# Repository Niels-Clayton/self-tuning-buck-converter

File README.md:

# [Self Tuning Buck Converter](https://niels-clayton.github.io/self-tuning-buck-converter/)

### Documents

Documentation and project planing

### Literature

Latex bibliography `.bib` file, organised using [JabRef](http://www.jabref.org), with copies of all cited documents.

### Reports

Latex projects for all written reports.

- Project Proposal
- Preliminary Report
- Final Project Report

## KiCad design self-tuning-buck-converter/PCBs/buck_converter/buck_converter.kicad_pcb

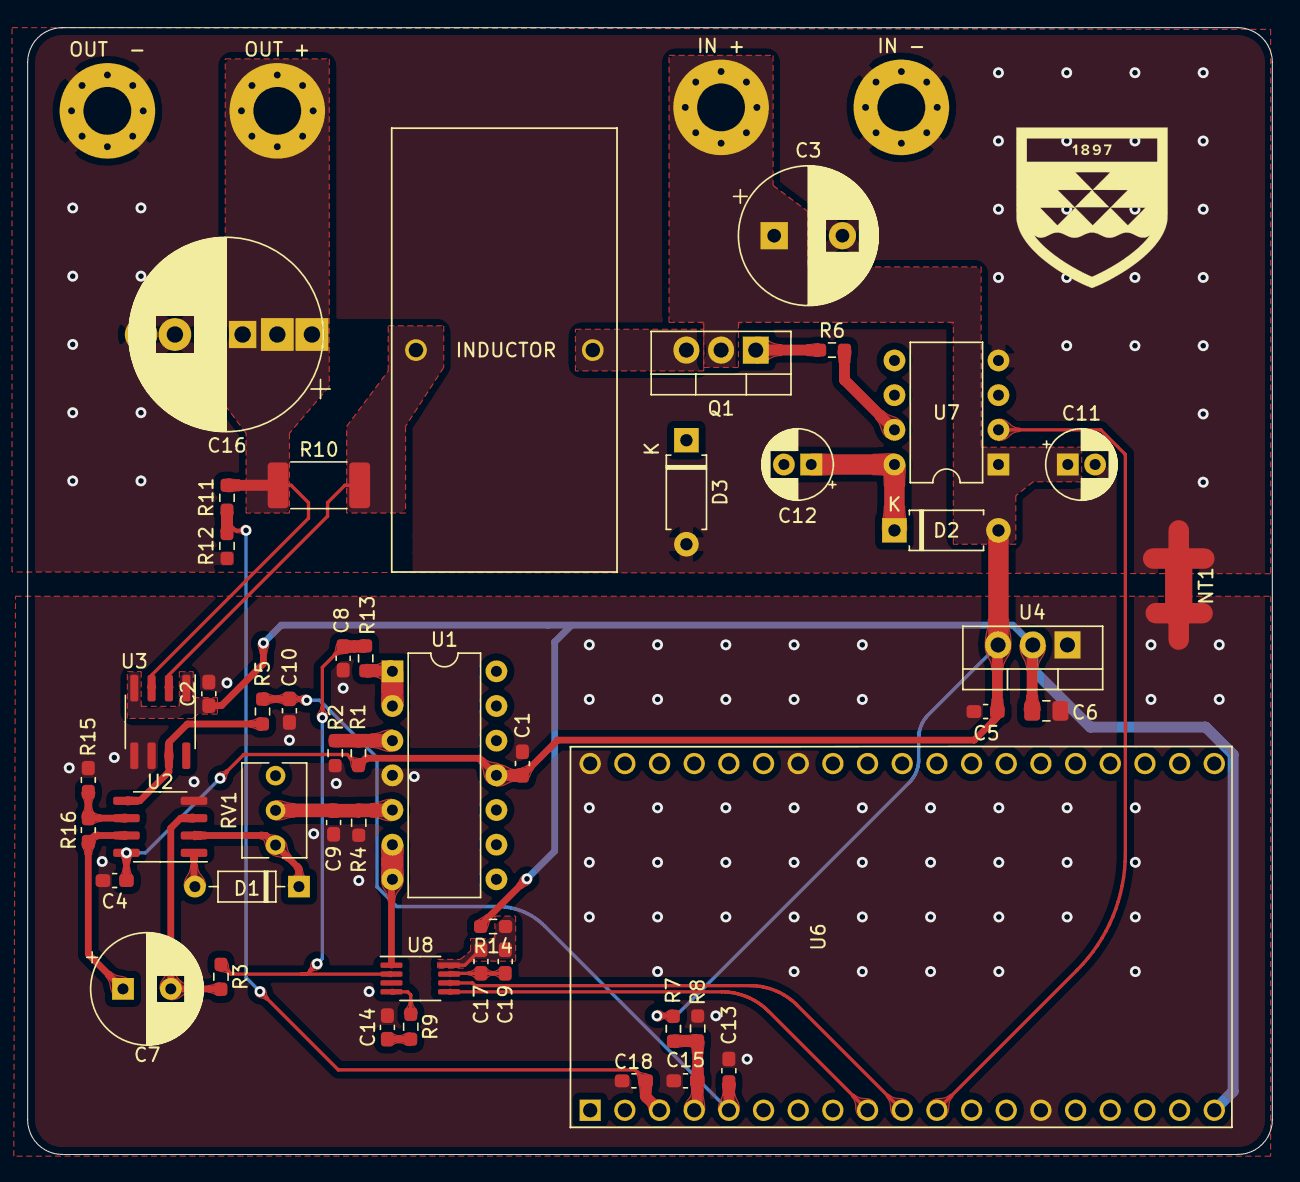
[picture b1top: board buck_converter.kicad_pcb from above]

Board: 2 copper layers, 91.2 x 82.6 mm, 53 parts (0 on the bottom side), 31 nets.

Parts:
C1, C2, C4, C13, C14, C15, C17, C18: 0.1u 16V; C_0603_1608Metric_Pad1.08x0.95mm_HandSolder
C3: 100u 50V; CP_Radial_D10.0mm_P5.00mm
C5, C9: 100n 16V; C_0603_1608Metric_Pad1.08x0.95mm_HandSolder
C6: 10u 16V; C_0805_2012Metric_Pad1.18x1.45mm_HandSolder
C7: 100u 16V; CP_Radial_D8.0mm_P3.50mm
C8, C10: 1u 16V; C_0603_1608Metric_Pad1.08x0.95mm_HandSolder
C11, C12: 10u 50V; CP_Radial_D5.0mm_P2.00mm
C16: 470u 50V; multi_cap
C19: 4.7u 16V; C_0603_1608Metric_Pad1.08x0.95mm_HandSolder
D1: 1N4148W; D_DO-35_SOD27_P7.62mm_Horizontal
D2, D3: D_Schottky; D_A-405_P7.62mm_Horizontal
IN +: VCC_IN; MountingHole_3.5mm_Pad_Via
IN -: GND_IN; MountingHole_3.5mm_Pad_Via
INDUCTOR: L; IND_HCTI-150-5.0
NT1: Net-Tie_2; NetTie-2_SMD_Pad2.0mm
OUT  -: LOAD -; MountingHole_3.5mm_Pad_Via
OUT +: LOAD +; MountingHole_3.5mm_Pad_Via
Q1: NMOS; TO-220-3_Vertical
R1, R2: 100k; R_0603_1608Metric_Pad0.98x0.95mm_HandSolder
R3: 10k; R_0603_1608Metric_Pad0.98x0.95mm_HandSolder
R4: 1M; R_0603_1608Metric_Pad0.98x0.95mm_HandSolder
R5, R13: 16k; R_0603_1608Metric_Pad0.98x0.95mm_HandSolder
R6: 10; R_0603_1608Metric_Pad0.98x0.95mm_HandSolder
R7: 560k; R_0603_1608Metric_Pad0.98x0.95mm_HandSolder
R8: 120k; R_0603_1608Metric_Pad0.98x0.95mm_HandSolder
R9: 2k; R_0603_1608Metric_Pad0.98x0.95mm_HandSolder
R10: 60m; R_2512_6332Metric_Pad1.52x3.35mm_HandSolder
R11: 56k; R_0603_1608Metric_Pad0.98x0.95mm_HandSolder
R12: 22k; R_0603_1608Metric_Pad0.98x0.95mm_HandSolder
R14: 5; R_0603_1608Metric_Pad0.98x0.95mm_HandSolder
R15, R16: 10k; R_0603_1608Metric_Pad1.05x0.95mm_HandSolder
RV1: 100; Potentiometer_Bourns_3266Y_Vertical
U1: TLO84CN; DIP-14_W7.62mm
U2: OPA2830; SOIC-8_3.9x4.9mm_P1.27mm
U3: LT1999-50; SOIC-8_3.9x4.9mm_P1.27mm
U4: LD1117V50; TO-220-3_Vertical
U6: ESP32-DEVKITC-32D; MODULE_ESP32-DEVKITC-32D
U7: IR2125; DIP-8_W7.62mm
U8: MAX11644; MSOP-8_3x3mm_P0.65mm

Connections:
+5V: C2.2, C6.1, R14.2, U3.1, U3.4, U4.2, U6.19
+12V: C1.2, C3.1, C4.2, C5.1, C11.1, D2.2, IN +.1, Q1.2, R1.1, R7.1, U1.11, U2.8, U4.3, U7.1
/sen_p: INDUCTOR.2, R10.2, U3.2
Avg_voltage: C10.2, C13.2, R5.1, U6.5
GND: C3.2, C11.2, C16.2, D3.2, IN -.1, NT1.1, OUT -.1, R12.2, U7.4
GNDD: C1.1, C2.1, C4.1, C5.2, C6.2, C8.1, C9.1, C10.1, C13.1, C14.2, C15.1, C18.1, NT1.2, R2.2, R4.1, R8.2, R15.2, U1.4, U2.4, U3.5, U3.6, U4.1, U6.14, U6.20, U6.26
unnamed: C7.2, R3.2, U2.3
unnamed: C9.2, R4.2, RV1.2, U1.5
unnamed: C12.1, D2.1, U7.8
unnamed: C12.2, D3.1, INDUCTOR.1, Q1.3, U7.5, U7.6
unnamed: C14.1, R9.2
unnamed: C17.1, C19.1, R14.1, U8.8
unnamed: C17.2, C19.2, U8.7
unnamed: D1.1, RV1.1, U2.2
unnamed: D1.2, U2.1
unnamed: Q1.1, R6.1
unnamed: R1.2, R2.1, U1.3
unnamed: R6.2, U7.7
unnamed: R9.1, U8.4
unnamed: R13.2, U1.1, U1.2
unnamed: R15.1, R16.2, U2.6
PWM: U6.11, U7.2
Pk_voltage: U1.6, U1.7, U8.1
SCL: U6.9, U8.5
SDA: U6.10, U8.6
Sense_avg: R5.2, U2.5, U3.7
Sense_ripple: C7.1, R16.1, U2.7
V_load: C16.1, OUT +.1, R10.1, R11.1, U3.3
V_ref: C8.2, R3.1, R13.1, U8.2
V_supply: C15.2, R7.2, R8.1, U6.4
load_sense: C18.2, R11.2, R12.1, U6.3

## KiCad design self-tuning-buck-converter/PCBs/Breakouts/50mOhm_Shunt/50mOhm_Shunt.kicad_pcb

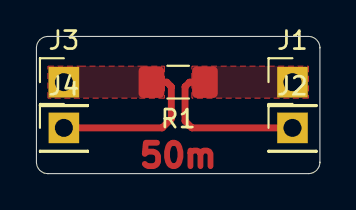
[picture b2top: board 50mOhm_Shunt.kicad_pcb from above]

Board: 2 copper layers, 15.7 x 7.6 mm, 5 parts (0 on the bottom side), 2 nets.

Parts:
J1: Input +; PinHeader_1x01_P2.54mm_Vertical
J2: Kelvin +; PinHeader_1x01_P2.54mm_Vertical
J3: Input -; PinHeader_1x01_P2.54mm_Vertical
J4: Kelvin -; PinHeader_1x01_P2.54mm_Vertical
R1: 50mOhm; R_1206_3216Metric_Pad1.42x1.75mm_HandSolder

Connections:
unnamed: J1.1, J2.1, R1.2
unnamed: J3.1, J4.1, R1.1

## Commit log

2018-04-30 Initial commit of ENGR 489 project template.
2018-05-07 Amendments to Report(s) directories.
    Rename 'Report' to 'Reports' and create subdirectories 'Preliminary Report' and 'Final Report', each with 'Figures' sub-folders.
2018-05-07 Addition of Presentations folder, rename of Reports markdown file, and amendments to the README file.
2018-05-07 Addition of preliminary/proposal and final report LaTeX templates. Minor amendment to the Literature section of the README file.
2018-05-07 Addition of the preliminary/proposal report template PDF.
2018-05-08 Locally typeset versions of reports.
2021-03-04 Update Markdown documents for consistency with the 2021 offering
2021-03-05 Fix incorrect name for Project Proposal directory
2021-03-10 Setup Project proposal LaTeX
2021-03-13 Update project proposal title
2021-03-15 Project proposal introduction
2021-03-19 proposal introduction
2021-03-19 Update bib
2021-03-19 Project Proposal Complete
2021-03-19 updated refrences
2021-04-02 Setup jabRef
2021-04-06 Update the evaluation section of the project proposal
2021-04-06 SPICE simulation of analog based PWM generation using an integrator to produce a triangle waveform.
2021-04-07 update gitignore
2021-04-08 Completed SPICE simulation of an intergrator op amp based PWM generator #4
2021-04-08 Began the writeup of the anaogue PWM section of the design #4
2021-04-12 Litrature to add to the bibliography #9
2021-04-19 Test the ESP32's capability to produce variable frequency PWM #5
2021-04-19 Update the PWM test code #5
2021-04-20 Tested the PWM in the lab and looked at the output on a scope. The frequency and duty cycle are both variable and independant, and the frequency step size is a maximum of 200Hz in the 90kHz - 100kHz 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
2021-05-16 Begin preliminary report, setup the template and write the abstract
2021-05-16 update the proposal, and remove the redundant word document
2021-05-16 Complete the setup of the prelim report
2021-05-18 Laid out the schaffolding for the report
2021-05-19 Prelim report
2021-05-19 Found some sources for buck converter design, and began wiring the buck converter background section of the report
2021-05-19 update references
2021-05-22 system overview
2021-05-22 Buck converter background section
2021-05-22 Proposal
2021-05-23 Background section complete
2021-05-23 This report big doo doo, it's 2:40am and im going insane drinking coffee out of a bowl
2021-05-24 Prelim report complete
2021-05-25 update gitignore to include vscode
2021-07-24 Implemented a different rectifier design
2021-07-25 Precision rectifier design and spice simulation
2021-07-26 updated the precision rectifier with a 50MHz bandwidth opamp, also designed a peak detictor circuit that is capable of accuratly matching and sustaining peak voltages between 100mV and 10V
2021-07-29 Various peak detecor circuits
2021-07-29 Updated the refrences within bibtex, to group refrences for easier sorting. also added refrences for analog designs of precision rectifiers and peak detection citcuits
2021-07-29 Created a bill of materials for all of the parts I want to test my current sensing desings
2021-08-09 this is still broke and i am broken too... please god help me... there are too many op-amps to pick from and I dont know why none of them will work... there are also very few working simulations of a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
2021-08-10 update peak detector
2021-08-11 update sim of peak detector
2021-08-17 created new BOM
2021-08-17 created shunt resistor breakouts for breadboard
2021-08-17 update breakout PCB's for the 50mO and 60mO resistors. Ordered the missing parts
2021-08-18 Due to covid I will be unable to getthe correct gate driver for some period of time. To be able to continute I have used a BJT to step up and invert the 3.3V logic output to 10V, allowing me to drive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
2021-08-19 updated breakout PCB's
2021-08-22 Created a bootsrapping circuit for driving the power mosfet with the esp32 micro. Wrote an API to interact the ADC hardware on the esp32, and then characterised the output of the ADC. It was found th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
2021-08-25 updated state space model
2021-08-26 updated the adc calibration code
2021-08-26 refactor directories and added a state space model of the buck converter
2021-08-26 added sources for control system design
2021-08-27 Designed a PI Controller for my state space model of my buck converter
2021-08-28 refactored code
2021-08-28 update adc code
2021-08-28 renamed controll system
2021-08-30 Update ADC headder
2021-08-30 refoctor and update PWM header and testing
2021-08-30 Created a PID output voltage controller. This controller was designed with matlab, based on a state space model of the output voltage. This controller is implemented such that it can be run within it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
2021-08-30 add terminal input for selectable output voltage
2021-09-03 update controller
2021-09-06 updated buck converter controller model
2021-09-06 began PCB design for entire buck converter
2021-09-06 update gate driver schematic
2021-09-14 refactor headder libraries, corrected load voltage divider
2021-09-14 Updated the internal esp ADC library to facilitate reading from multiple pins. This new implementation requires the instantiation of an esp_adc struct, which will hold the adc channel, as well as the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
2021-09-14 updated the graphics for the buck converter state opperation
2021-09-14 updated the resistor values of the output load voltage divider. This will provide a more accurate measurment of the output load voltage
2021-09-14 updated the voltage control loop to use the new implementation of the ADC API
2021-09-15 Replaced the output load sensing voltage divider with more accurate resistors, then updated the code to use the new resistor values
2021-09-17 Re-Structure the codebase to implent using single headder libraries
2021-09-17 Updated the PID controll loop to measure the input supply voltage. This allows for accurate control of the output voltage, when the supply voltage varies and changes.
2021-09-17 speed improvments for code, addition of IRAM_ATTR to time sensetive functions
2021-09-18 small testing
2021-09-18 Set up the final report chapter structure. Wrote a basic scafolding of the new background sections.
2021-09-18 added sections and some short descriptions to the design section
2021-09-19 why is this report so hard to write :(
2021-09-19 Final report design section writing
2021-09-19 add someheadding for the implementation and evaluation chapters
2021-09-19 updated the code for the final report
2021-09-20 Fixed buffer overflow of the rilling average buffer
2021-09-22 updated pcb schematic, added the current sense amplifier, ripple averager (low pass filter), and ripple peak detector
2021-09-22 updated schematic with bypass capacitors, and added small filter caps to the ESP32's ADC input pins as recomended by the the datasheet
2021-09-23 updated the design of the peak detectror such that is imposes thepeaks on VCC/2. This voltage will vary as VCC shifts, but the differential ADC can be used to take accurate peak readings regardless, 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
2021-09-23 Finalised PCM and selected component footprints
2021-09-25 Updated schematic with edits found from building it in the lab
2021-09-26 Completed the data collection on the performance of the new peak detection circuit
2021-09-27 updated peak detector error plots
2021-09-27 PEak detection evaluation
2021-09-27 PWM evaluation plots
2021-09-27 begin and almost complete the PCB design of the buck converter:
2021-09-28 Matlab code to process the PWM frequency and duty cycle data
2021-09-28 evaluated the PWM and the duty cycle
2021-09-28 evaluated the controller output, plotting the step response of the controller, aswell as the output regulation to changing VCC
2021-09-29 completed the PCB design
2021-09-29 added via stitching to the board
2021-09-29 update report
2021-09-29 many images added for the final report... also tidied up the schematic for input into the report
2021-09-29 esported images to svg
2021-09-30 moved the evaluation data for the peak detector into matlab. generated plots of all the data
2021-09-30 PWM Error plotting changed to a percentage of the target value
2021-09-30 converted svg images to pdf's for inclusion in the report
2021-10-01 created plots for the PWM generation
2021-10-01 create figures
2021-10-01 create plots for ADC calibration
2021-10-01 updated figure
2021-10-02 make even more images omg... How will I fit all these images
2021-10-02 updated the precision rectifier simulation
2021-10-03 added 150mV ripple table
2021-10-03 fixed compilation errors
2021-10-03 update appendix structure, included all code with the correct listings settings, and finished inputting the peak detector error tables
2021-10-03 update PWM appendix
2021-10-03 added more immags to the appendix
2021-10-03 Finished the control and peak detector sections of the appendix
2021-10-04 completed the appendix
2021-10-05 hot garbage
2021-10-05 finished the introduction
2021-10-05 Update the digital PWM section of background
2021-10-05 current sensing background
2021-10-05 update current sensing background
2021-10-06 finished the introduction and background. Rewrote the system specifications section of the design.
2021-10-06 added control system matlab simulation figure
2021-10-07 close to completing the design section
2021-10-08 completed the design section
2021-10-08 start implementation
2021-10-09 Implemented suggestions from supervisor
2021-10-09 System implemnttion complete.
2021-10-09 setup the evaluation structure
2021-10-10 It's done.
2021-11-23 update PCB, and create the iBOM
2021-11-23 generate gerbers
2021-11-23 update docs
2021-11-23 removed un-necessay schematics
2022-04-11 update to kicad 6
